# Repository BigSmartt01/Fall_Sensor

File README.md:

# Fall Sensor - ESP32-C3 Wearable Fall Detection System

## Overview

<p align="center">
  <br>
  <em>3D render of the Fall Sensor carrier PCB (v1, single-layer)</em>
</p>

An intelligent wearable fall detection system built on the ESP32-C3 Super Mini with BMI160 IMU, targeting elderly users with waist/lower-back placement. The system combines a 4-stage rule-based state machine with an on-device CNN (TFLite Micro, int8 QAT) for high-confidence detection. A persistent alerted state holds the alert active until the person's posture changes or they self-dismiss, preventing the common problem of fall alerts clearing while the person is still on the floor.

Real-time data streams over WiFi TCP to a PyQtGraph dashboard and InfluxDB/Grafana stack for threshold tuning and post-event analysis. A dual-purpose button handles both "I'm okay" dismissal and manual "I need help" alerts.

## Hardware

| Component | Part | Notes |
|---|---|---|
| MCU | ESP32-C3 Super Mini | USB-CDC, BLE, WiFi |
| IMU | BMI160 | I2C 0x68, ODR 200Hz |
| Charger | TP4056 | LiPo, 4.2V cutoff |
| Boost converter | MT3608 | Battery -> 5V rail |
| Buzzer | Passive buzzer | Active LOW driver |
| Button | Tactile switch | Dual-purpose: dismiss/SOS |
| Board | 5x7cm perfboard | Power/signal zone separated |

| Board | 5x7cm perfboard | Power/signal zone separated |

<p align="center">
  <br>
  <em>Hand-soldered perfboard build, ESP32-C3 Super Mini + BMI160</em>
</p>

**Pin assignments (ESP32-C3 Super Mini):**

| Pin | Function |
|---|---|
| GPIO8 | SDA (BMI160) |
| GPIO9 | SCL (BMI160) |
| GPIO2 | Buzzer |
| GPIO3 | Button (INPUT_PULLUP, active LOW) |
| GPIO4 | BMI160 INT1 (reserved) |
| GPIO5 | BMI160 INT2 (reserved) |

**Power path:** LiPo -> TP4056 (charge management) -> MT3608 (boost to 5V) -> ESP32-C3 5V pin -> onboard LDO -> 3.3V rail -> BMI160 VCC

## Project Structure

```
Fall_Sensor/
├── firmware_idf/                    # ESP-IDF project (active)
│   ├── CMakeLists.txt
│   ├── partitions.csv               # custom 3MB app partition for ESP32-C3 4MB flash
│   ├── sdkconfig.defaults
│   ├── main/
│   │   ├── CMakeLists.txt
│   │   ├── fall_sensor.cpp          # app_main() entry point
│   │   ├── main.cpp                 # state machine + BMI160 + tasks
│   │   ├── inference.cpp            # TFLite Micro wrapper + consecutive filter
│   │   ├── inference.h
│   │   ├── wifi_stream.cpp          # WiFi TCP server for dashboard streaming
│   │   ├── wifi_stream.h
│   │   └── fall_model.h             # auto-generated model C header
│   └── components/
│       ├── esp-tflite-micro/        # git submodule (espressif official)
│       ├── DFRobot_BMI160/          # git submodule (unmodified)
│       └── DFRobot_BMI160_wrapper/  # local CMakeLists.txt wrapper (tracked)
├── firmware/                        # legacy PlatformIO attempt - kept for reference
├── docs/
│   ├── ERRORS_AND_FIXES.md
│   └── ML_README.md
├── hardware/                        # KiCad schematics, BOM, perfboard layout
├── visualization/
│   ├── bridge.py                    # Serial to InfluxDB bridge
│   ├── dashboard.py                 # PyQtGraph dashboard (serial + WiFi TCP modes)
│   └── docker-compose.yml           # InfluxDB + Grafana stack
├── tests/
│   ├── three_classes/               # ML training pipeline
│   │   ├── inspect_dataset.py
│   │   ├── train_cnn.py
│   │   ├── train_qat.py
│   │   ├── quantize_model.py
│   │   ├── check_model.py
│   │   ├── convert_to_header.py
│   │   ├── list_ops.py
│   │   └── fall_cnn_qat_int8.tflite
│   └── edge_impulse_sample_v3/      # balanced SE-weighted sample (not tracked)
├── requirements.txt
├── .gitignore
└── README.md
```

## Cloning

This project uses git submodules. Clone with:

```bash
git clone --recurse-submodules <repo-url>
```

If already cloned:

```bash
git submodule update --init --recursive
```

## Building and Flashing

Open ESP-IDF terminal in VS Code (`Ctrl+Shift+P` -> ESP-IDF: Open ESP-IDF Terminal):

```bash
cd firmware_idf
idf.py set-target esp32c3
idf.py build
idf.py -p COM7 flash monitor
```

Exit monitor: `Ctrl+]`

On first build after a clean or target change, delete `sdkconfig` (not `sdkconfig.defaults`) before running `set-target` to avoid stale target conflicts.

## How It Works

### State Machine

```
STATE_NORMAL
  accelMag < 3.0 m/s²  ->  STATE_FREEFALL  (timeout 400ms)
  
STATE_FREEFALL
  accelMag > 20.0 m/s² ->  STATE_IMPACT    (window 500ms)
  
STATE_IMPACT
  gyroMag < 25 deg/s   ->  STATE_POST_IMPACT_STILLNESS
  
STATE_POST_IMPACT_STILLNESS
  stillness 2.5s + orientation change + NN confirms  ->  STATE_FALL_CONFIRMED
  
STATE_FALL_CONFIRMED
  captures fall orientation, triggers buzzer, fires FALL event
  ->  STATE_FALL_ALERTED  (persistent - does not auto-clear)
  
STATE_FALL_ALERTED
  re-buzzes every 10s
  posture change > 2.0 m/s² delta  ->  STATE_NORMAL
  button press ("I'm okay")        ->  STATE_NORMAL
```

Any state: button press outside STATE_FALL_ALERTED -> manual "I need help" alert

### ML Inference

- Model: lightweight 1D CNN, int8 QAT, 16.9KB flash, 47.1KB RAM
- Input: 512-sample sliding window of accel Y (in g) at 200Hz = 2.56 second window
- Consecutive filter: 3 consecutive runs >= 80% probability required before confirming
- Falls back to rule-based alone if window not yet full

### Sensor Configuration

BMI160 ODR set to 200Hz via direct register write after I2cInit():

```cpp
Wire.beginTransmission(0x68);
Wire.write(0x40); Wire.write(0x09);  // ACC_CONF: 200Hz
Wire.endTransmission();

Wire.beginTransmission(0x68);
Wire.write(0x42); Wire.write(0x09);  // GYR_CONF: 200Hz
Wire.endTransmission();
```

BMI160 init order matters: `softReset()` must be called before `I2cInit()`. Reversed order causes silent all-zero readings.

## Serial/WiFi Output Format

```
DATA,<timestamp_ms>,<accelMag>,<gyroMag>,<state>
FALL,<timestamp_ms>
```

State values: 0=NORMAL, 1=FREEFALL, 2=IMPACT, 3=POST-IMPACT STILLNESS, 4=FALL CONFIRMED, 5=FALL ALERTED

Output goes to both USB Serial (printf) and WiFi TCP simultaneously.

## Visualization

### Dashboard (PyQtGraph)

```bash
cd visualization
python dashboard.py
```

Switch between serial and WiFi at the top of the file:

```python
CONNECTION_MODE = "serial"   # or "wifi"
WIFI_HOST       = "192.168.x.x"   # ESP32-C3 IP printed on boot
WIFI_PORT       = 3333
```

The ESP32-C3 IP is printed on boot: `[WiFi] Connect dashboard with: TCP <IP>:3333`

<p align="center">
  <br>
  <em>Live dashboard showing a detected fall event: freefall, impact, then post-impact stillness</em>
</p>

### InfluxDB + Grafana

```bash
cd visualization
docker compose up -d
```

- InfluxDB: http://localhost:8086 (bucket: fallsensor, org: smartlab)
- Grafana: http://localhost:3000

## ML Pipeline

See [docs/ML_README.md](docs/ML_README.md) for full training and quantization details.

Quick retrain after any model or dataset change:

```bash
cd tests/three_classes
venv_compat\Scripts\activate    # Python 3.10 required - TF not yet on 3.13+
python train_qat.py
python convert_to_header.py     # outputs firmware_idf/main/fall_model.h
cd ../../firmware_idf
idf.py build
idf.py -p COM7 flash monitor
```

### Current Model Performance

| Metric | Value |
|---|---|
| Overall accuracy | 95.21% |
| Fall recall | 97.38% |
| ADL recall | 95.16% |
| Flash | 16.9 KB |
| Inference RAM | 47.1 KB |
| Window | 512 samples at 200Hz = 2.56s |

## Python Dependencies

```bash
pip install -r requirements.txt
```

ML training scripts require Python 3.10 in a separate venv (`venv_compat`) - TensorFlow does not support Python 3.13+.

## Future Work

- PCB design: 2-layer board, BMI160 and ESP32-C3 Super Mini as soldered modules on carrier, discrete power section
- Enclosure: TPU 3D printed, waist/belt-clip form factor
- BLE alert path for phone app connectivity
- SIM/GPS module on existing 5V rail for cellular fallback
- BMI160 INT1/INT2 for hardware step detection and low-power motion-wake
- Collect real elderly fall simulation data for model fine-tuning

## Troubleshooting

See [docs/ERRORS_AND_FIXES.md](docs/ERRORS_AND_FIXES.md)

## Author

Smart Ayodele
ayosmart129@gmail.com

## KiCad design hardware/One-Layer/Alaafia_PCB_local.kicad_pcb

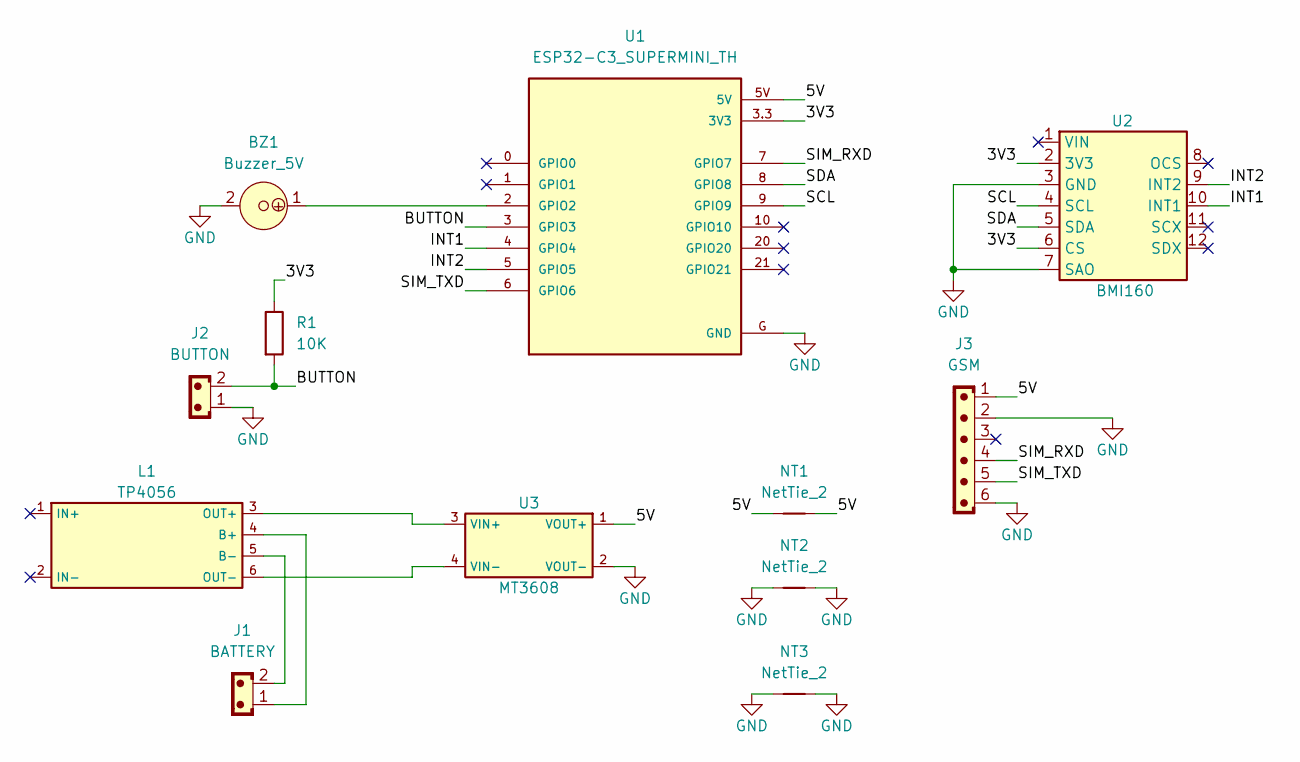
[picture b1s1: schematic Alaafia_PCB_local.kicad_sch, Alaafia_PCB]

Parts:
BZ1: Buzzer_5V; MagneticBuzzer_ProSignal_ABT-410-RC
J1: BATTERY; JST_EH_B2B-EH-A_1x02_P2.50mm_Vertical
J2: BUTTON; JST_EH_B2B-EH-A_1x02_P2.50mm_Vertical
J3: GSM; JST_EH_B6B-EH-A_1x06_P2.50mm_Vertical
L1: TP4056
NT1, NT3: NetTie_2; JUP_P5.08mm
NT2: NetTie_2; JUP_P14mm
R1: 10K; R_Axial_DIN0411_L9.9mm_D3.6mm_P15.24mm_Horizontal
U1: ESP32-C3_SUPERMINI_TH; MODULE_ESP32-C3_SUPERMINI_TH
U2: BMI160
U3: MT3608

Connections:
/3V3: R1.1, U1.3.3 (3V3), U2.2 (3V3), U2.6 (CS)
/5V: J3.1, NT1.1, NT1.2, U1.5V, U3.1 (VOUT+)
/BUTTON: J2.2, R1.2, U1.3 (GPIO3)
/INT1: U1.4 (GPIO4), U2.10 (INT1)
/INT2: U1.5 (GPIO5), U2.9 (INT2)
/SCL: U1.9 (GPIO9), U2.4 (SCL)
/SDA: U1.8 (GPIO8), U2.5 (SDA)
/SIM_RXD: J3.4, U1.7 (GPIO7)
/SIM_TXD: J3.5, U1.6 (GPIO6)
GND: BZ1.2, J2.1, J3.2, J3.6, NT2.1, NT2.2, NT3.1, NT3.2, U1.G (GND), U2.3 (GND), U2.7 (SAO), U3.2 (VOUT-)
unnamed: J1.1, L1.4 (B+)
unnamed: J1.2, L1.5 (B-)
unnamed: L1.3 (OUT+), U3.3 (VIN+)
unnamed: L1.6 (OUT-), U3.4 (VIN-)
unnamed: BZ1.1, U1.2 (GPIO2)

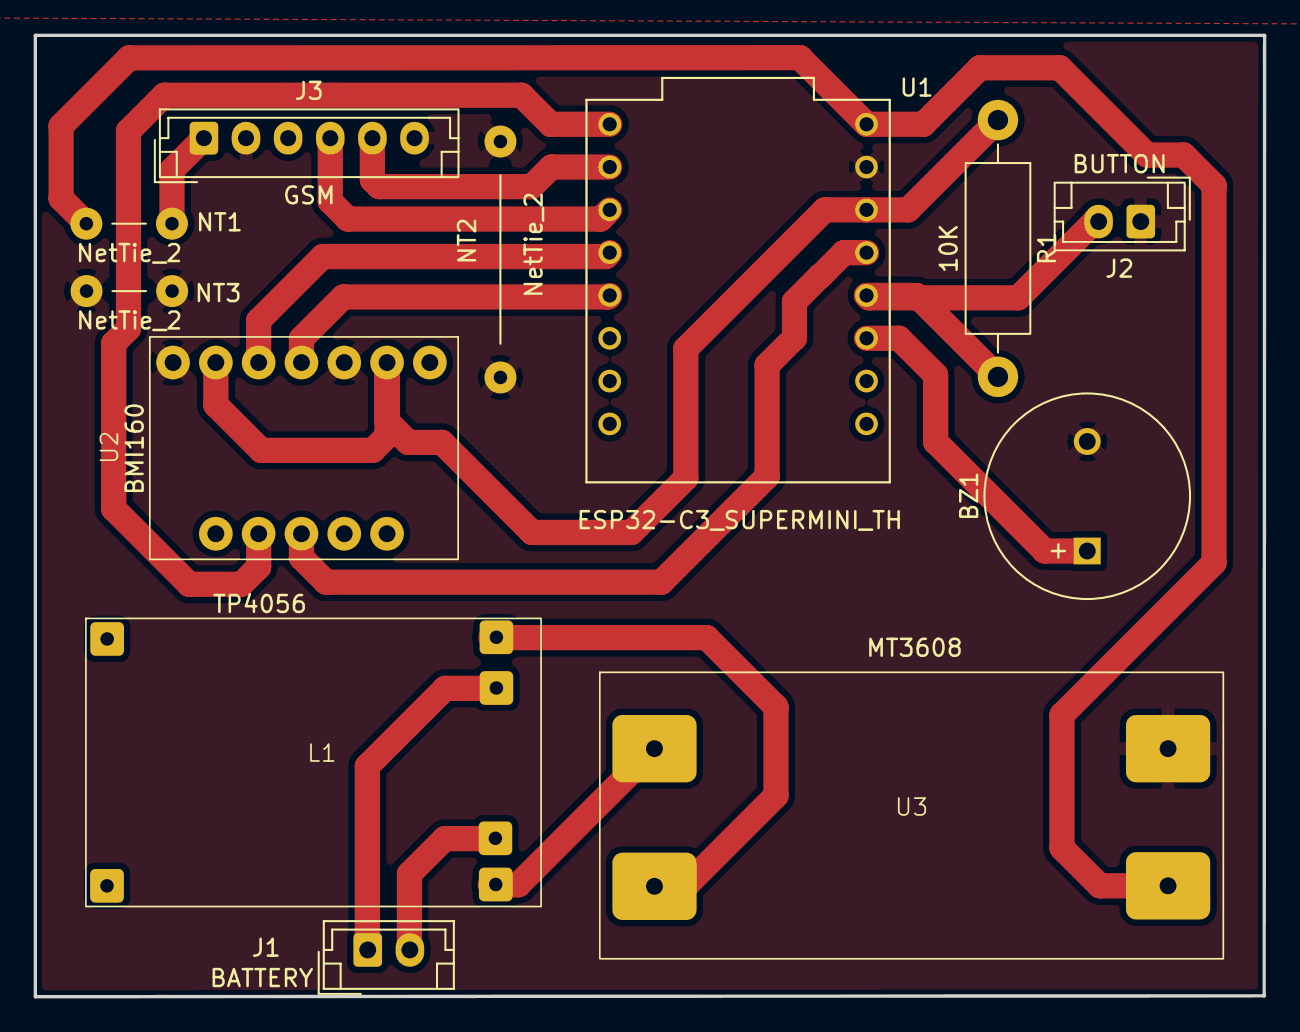
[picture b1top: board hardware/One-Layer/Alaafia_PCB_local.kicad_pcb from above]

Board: 2 copper layers, 72.9 x 57.0 mm, 12 parts (0 on the bottom side), 15 nets.

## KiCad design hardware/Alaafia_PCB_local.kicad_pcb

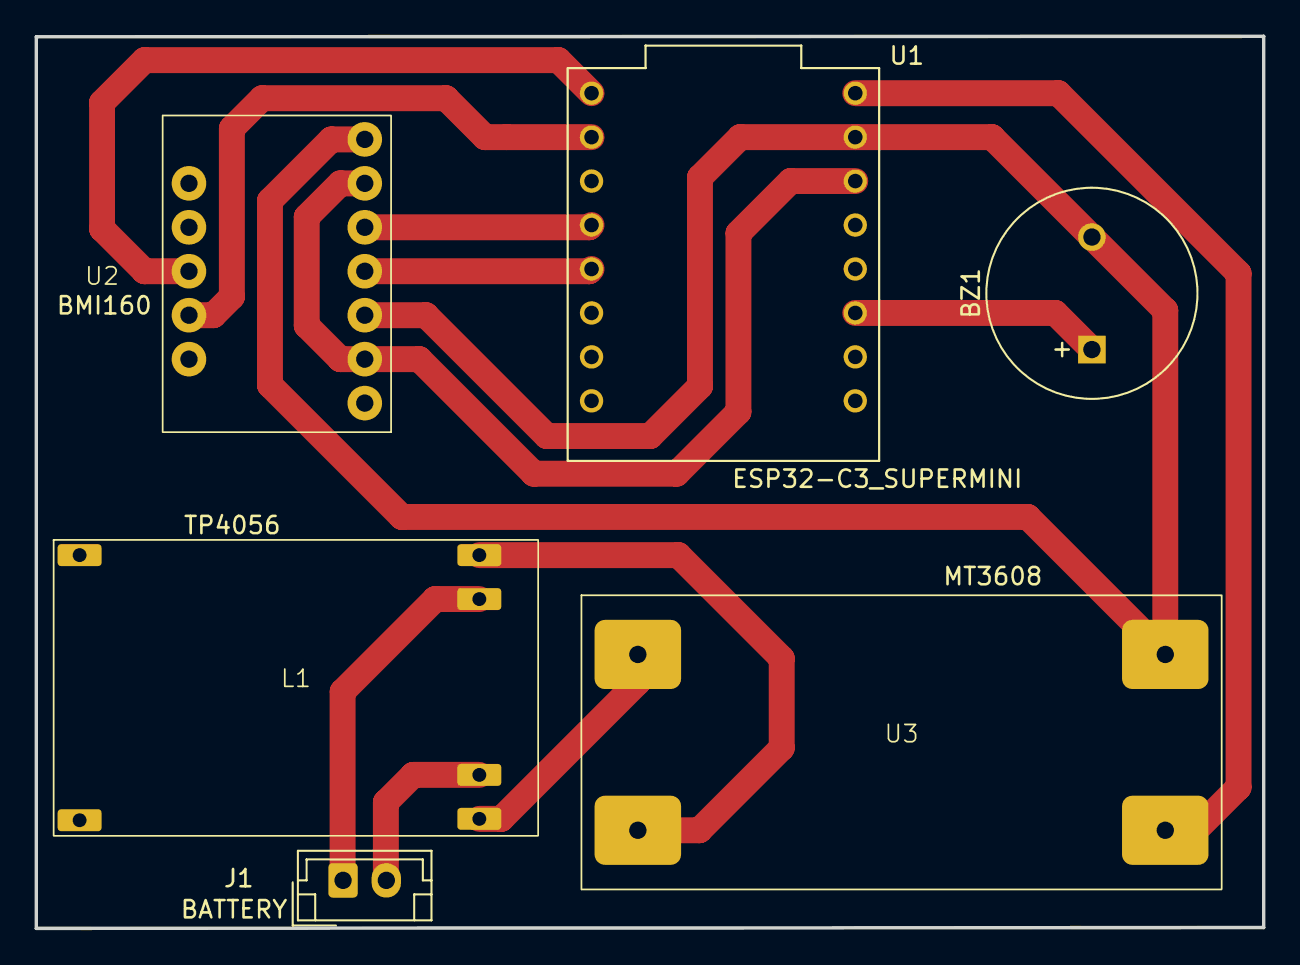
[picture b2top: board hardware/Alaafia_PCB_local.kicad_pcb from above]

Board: 2 copper layers, 70.9 x 51.5 mm, 6 parts (0 on the bottom side), 12 nets.

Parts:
BZ1: Buzzer_5V; MagneticBuzzer_ProSignal_ABT-410-RC
J1: BATTERY; JST_EH_B2B-EH-A_1x02_P2.50mm_Vertical
L1: TP4056
U1: ESP32-C3_SUPERMINI; MODULE_ESP32-C3_SUPERMINI_TH
U2: BMI160
U3: MT3608

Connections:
/3V3: U1.3.3 (3V3), U2.2 (3V3), U2.6 (CS)
/5V: U1.5V, U3.3 (VOUT+)
/GND: BZ1.2, U1.G (GND), U2.3 (GND), U2.7 (SAO), U3.4 (VOUT-)
/INT1: U1.5 (GPIO5), U2.10 (INT1)
/INT2: U1.6 (GPIO6), U2.11 (INT2)
/SCL: U1.9 (GPIO9), U2.4 (SCL)
/SDA: U1.8 (GPIO8), U2.5 (SDA)
unnamed: J1.1, L1.3 (B+)
unnamed: J1.2, L1.4 (B-)
unnamed: L1.1 (OUT+), U3.1 (VIN+)
unnamed: L1.2 (OUT-), U3.2 (VIN-)
unnamed: BZ1.1, U1.2 (GPIO2)

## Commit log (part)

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2026-05-21 Folder structure
2026-05-21 Grafana working
2026-05-21 pygraph plotter
2026-05-22 Updated MD files
2026-05-22 Added test
2026-05-29 First model trained locally
2026-06-01 ML pipeline code addition
2026-06-03 Trying to push
2026-06-05 Large Dataset sorted
2026-06-05 Push
2026-06-05 Dataset link added
2026-06-08 One layer designed
2026-06-08 TFLite Library dependency
2026-06-14 Migrated to IDF
2026-06-17 Initial commit with all files
2026-06-18 Remove esp-tflite-micro from index to re-add as submodule
2026-06-18 Add esp-tflite-micro as submodule
2026-06-18 I2C error off, but not responidng yet
2026-06-18 Added debug lines for setup and initarduino
2026-06-19 Before pulling idf framework
2026-06-19 repoint DFRobot_BMI160 submodule to latest master
2026-06-19 add DFRobot_BMI160_wrapper component, remove abandoned PlatformIO tflite-micro attempt
2026-06-19 IDF and I2C responds with printf rather than Serial.print or Serial.printf
2026-06-30 Integrated WiFi streaming and dashboard for both serial and wifi
